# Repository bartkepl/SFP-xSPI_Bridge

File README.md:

# SFP-xSPI Bridge
## Mostek OCTOSPI / QUADSPI / SPI ↔ SFP na FPGA Gowin GW1N-9

Moduł łączący dwa mikrokontrolery STM32 łączem światłowodowym punkt–punkt, bez stosu IP. Host zapisuje i odczytuje ramki przez OCTOSPI, QUADSPI lub zwykłe SPI; FPGA koduje je w 8b/10b i wysyła przez moduł SFP z prędkością 100 Mbaud, a po drugiej stronie odzyskuje zegar programowo (soft-CDR z nadpróbkowaniem). Tryb przezroczysty UART pozwala użyć pary mostków jako „przedłużacza” portu szeregowego, bez żadnego sterownika.

> **Status:** projekt FPGA ukończony i zweryfikowany w symulacji (testy modułów i testy end-to-end dwóch kompletnych mostków), biblioteka C dla STM32 gotowa i przetestowana na modelu mostka, schemat i PCB rev. A zweryfikowane ([raport](doc/pcb-rev-a.md)), pliki produkcyjne wygenerowane — przed zamówieniem prototypu. Uruchomienie sprzętowe według [planu](doc/sfp-xspi-bridge-plan.md#9-plan-uruchomienia-bring-up).

```
STM32 ══ xSPI ══ GW1N-9 ══ LVDS ══ SFP ~~~ światłowód ~~~ SFP ══ LVDS ══ GW1N-9 ══ xSPI ══ STM32
```

---

## Płytka

<!-- Rendery generuje pcb/gen_media.kicad_jobset -->

| Góra (TOP) | Dół (BOTTOM) |
|---|---|
|  |  |

Płytka 4-warstwowa (JLC04161H-7628): pary LVDS na warstwie zewnętrznej nad ciągłą masą, płaszczyzna 3,3 V na warstwie wewnętrznej. Na płytce: klatka SFP, złącze hosta 2 × 10 (raster 1,27 mm), złącze programowania Tag-Connect TC2050 i zworka wyboru trybu. Zasilanie wyłącznie 3,3 V z hosta.

Wygenerowane PDF-y: [schemat](prod/sch/SFP_xSPI_Bridge.pdf) · [PCB](prod/pcb/SFP_xSPI_Bridge.pdf) · [interaktywny BOM](prod/ibom/SFP_xSPI_Bridge_ibom.html).

---

## Najważniejsze cechy

- **Łącze 100 Mbaud 8b/10b** przez standardowy moduł SFP bez wewnętrznego CDR (100BASE-FX / OC-3 lub 1000BASE-X, MM / SM, duplex lub BiDi).
- **Programowy odzysk zegara** — 4× nadpróbkowanie serializerami IDES8 (400 Msps), śledzenie fazy z histerezą, tolerancja odchyłki częstotliwości do ok. ±3900 ppm; oba końce na niezależnych generatorach, bez bufora elastycznego.
- **Ramki z CRC-32** (1–1024 B treści, pole TYPE do multipleksowania strumieni), kontrola przepływu XON/XOFF i gotowość odbiornika w sekwencji bezczynności — dane nie giną przy wolnym odbiorcy.
- **Interfejs hosta wzorowany na SPI NOR** — instrukcja i adres na 1 linii, dane na 1, 4 lub 8 liniach, SDR, tryb 0, SCLK do 40 MHz; współpracuje z OCTOSPI / XSPI / QUADSPI w trybie pośrednim i ze zwykłym SPI.
- **Spójne rejestry** — zatrzask przy opadnięciu CS, zapis stosowany po podniesieniu CS; FIFO TX 4 KiB i RX 8 KiB, przerwanie `HOST_IRQ_N`.
- **Tryb przezroczysty UART** — zworka lub rejestr; 8N1, 115 200 bit/s domyślnie, do ok. 3 Mbit/s, opcjonalnie RTS/CTS.
- **Zarządzanie modułem SFP** — I2C master w FPGA: pamięć A0h / A2h, automatyczny odczyt diagnostyki DDM, sygnały TX_DISABLE / TX_FAULT / LOS / MOD_ABS.
- **Diagnostyka łącza** — liczniki błędów kodu, CRC, długości, ramkowania, przepełnień i utrat synchronizacji; pętla zwrotna wewnątrz FPGA i echo ramek.
- **Biblioteka C dla STM32** konfigurowana przez `#define`, z portami HAL dla OCTOSPI, XSPI, QUADSPI i SPI.

---

## Specyfikacja

| Parametr | Wartość |
|---|---|
| FPGA | Gowin GW1N-UV9QN48C6/I5 (GW1N-9C), konfiguracja AUTOBOOT z wewnętrznej pamięci Flash |
| Łącze | 100 Mbaud, 8b/10b, ramki z CRC-32, bez retransmisji (błędy zgłaszane hostowi) |
| Przepustowość | do ok. 9,9 MB/s treści (ramki 1024 B) |
| Interfejs hosta | SPI 1-x-1, QSPI 1-0-4, OCTOSPI 1-0-8; SDR, tryb 0, SCLK ≤ 40 MHz |
| Bufory | FIFO TX 4 KiB, FIFO RX 8 KiB (BSRAM) |
| Tryb UART | 8N1, 115 200 bit/s (do ok. 3 Mbit/s), opcjonalnie RTS/CTS |
| Moduły SFP | INF-8074i, bez wewnętrznego CDR; SFP+ nieobsługiwane |
| Złącze hosta | 2 × 10, raster 1,27 mm: 3,3 V, SCLK, CS, IO0…IO7, DQS, IRQ, RST |
| Zasilanie | 3,3 V, ok. 0,45 A (moduł SFP do 300 mA) |
| PCB | 4 warstwy, 68 × 29,3 mm, 1,6 mm |
| Zajętość FPGA | 4483 LUT/ALU (52 %), 7 z 26 BSRAM; `clk_sys` 50 MHz (Fmax 56 MHz) |

---

## Architektura

```
             xSPI (SCLK ≤ 40 MHz)                                       LVDS 100 Mbaud
  STM32 ════════════════════════╗                                   ╔════════════════ SFP
                                ▼                                   │
          xspi_slave ─▶ csr_regs ─┬─▶ FIFO TX ─▶ framer + CRC ─▶ 8b/10b ─▶ OSER8 ─▶ TLVDS_OBUF ─▶ TD±
                                  │
                                  ├─◀ FIFO RX ◀─ deframer + CRC ◀─ 8b/10b ◀─ comma align ◀─ soft-CDR ◀─ IDES8 ◀─ RD±
                                  │
                                  ├─▶ I2C master + DDM ─▶ SFP SCL / SDA
                                  └─▶ sygnały SFP, LED, HOST_IRQ_N

  tryb UART:  UART_RX ─▶ pakietyzacja (ramki TYPE 0x01) ─▶ FIFO TX      FIFO RX ─▶ UART_TX
  zegary:     CLK_25M ─▶ rPLL 200 MHz (serializery) ─▶ CLKDIV /4 ─▶ clk_sys 50 MHz (logika)
```

Decyzje projektowe z uzasadnieniem: [rejestr ADR](doc/adr/README.md). Pełna koncepcja (piny, zegary, warstwa fizyczna, PCB, moduły, komendy, rejestry, uruchomienie): [`doc/sfp-xspi-bridge-plan.md`](doc/sfp-xspi-bridge-plan.md).

### Arkusze schematu

| Arkusz | Plik | Zawartość |
|---|---|---|
| root | [SFP_xSPI_Bridge.kicad_sch](pcb/SFP_xSPI_Bridge.kicad_sch) | połączenia hierarchiczne, otwory montażowe |
| EXT_IO | [ext_io.kicad_sch](pcb/ext_io.kicad_sch) | FPGA (zasilanie, konfiguracja, magistrala hosta), złącze hosta J3, Tag-Connect J2, zworki, TVS |
| SFP | [sfp.kicad_sch](pcb/sfp.kicad_sch) | klatka SFP, filtry zasilania modułu, terminacja i bias RX, generator 25 MHz, diody LED |

---

## Dokumentacja

| Dokument | Zawartość |
|---|---|
| [Interfejs hosta (datasheet)](doc/datasheet/index.md) | wyprowadzenia J3, parametry czasowe, komendy xSPI, mapa rejestrów, tryb UART, przykłady |
| [Biblioteka C (STM32)](doc/firmware.md) | konfiguracja, porty HAL, API, weryfikacja |
| [Koncepcja konstrukcji](doc/sfp-xspi-bridge-plan.md) | architektura, przydział pinów, zegary, PCB, moduły, uruchomienie |
| [Weryfikacja płytki rev. A](doc/pcb-rev-a.md) | DRC / ERC, zgodność z przydziałem pinów i INF-8074i, pary LVDS, zasilanie, pliki produkcyjne |
| [Projekt FPGA](doc/vhdl/index.md) | moduły VHDL, testbenche, symulacja, wyniki syntezy |
| [Testy end-to-end](doc/e2e/index.md) | dwa mostki połączone łączem: SPI, QSPI, OSPI, UART — z przebiegami |
| [Decyzje (ADR)](doc/adr/README.md) | kontekst, warianty i konsekwencje decyzji projektowych |

Dokumentacja jako serwis MkDocs (`mkdocs` 1.6, `mkdocs-material` 9.x):

```
python -m mkdocs serve        # podgląd: http://127.0.0.1:8000
```

---

## Szybki start

**FPGA** — Gowin EDA (projekt `vhdl/sfp_bridge/sfp_bridge.gprj`, VHDL-2008):

```
cd vhdl/sfp_bridge
gw_sh build.tcl               # synteza, PnR i bitstream
```

Bitstream: `vhdl/sfp_bridge/impl/pnr/sfp_bridge.fs`, programowanie przez JTAG (Gowin Programmer lub openFPGALoader).

**Symulacja** — GHDL 5 (VHDL-2008), na Windows w WSL; modele prymitywów z instalacji Gowin EDA:

```
$env:GOWIN_SIMLIB = "<Gowin EDA>\IDE\simlib\gw1n"   # PowerShell
cd vhdl\sim
.\run_tests.ps1               # wszystkie testbenche; .\view.ps1 <tb> — przebieg w GTKWave
```

**Firmware** — biblioteka w `firmware/sfp_bridge/`: skopiować `config/sfpb_config_template.h` jako `sfpb_config.h`, ustawić transport i uchwyt peryferium, wywołać `sfpb_init(&dev, NULL)`. Testy na PC: `make -C firmware/tests`.

**Bez hosta** — dwa mostki ze zwartą zworką `MODE_SEL` i dwa konwertery USB-UART (115 200 8N1) tworzą przezroczysty kanał szeregowy przez światłowód.

---

## Weryfikacja

| Obszar | Zakres | Wynik |
|---|---|---|
| Moduły FPGA | 24 samosprawdzające testbenche GHDL, testy mutacyjne | PASS |
| Łącze | dwa końce z odchyłką 200 ppm i jitterem, CDR do ±1000 ppm i ±0,3 UI | PASS |
| End-to-end | dwa kompletne mostki (modele prymitywów Gowin): SPI, QSPI, OSPI, UART zworką i rejestrem | PASS |
| Synteza | pełny układ, ograniczenia czasowe spełnione (`clk_sys` 56 MHz, `clk_host` 44 MHz) | OK |
| Biblioteka C | 207 sprawdzeń na modelu mostka, 17 mutacji wykrytych; kompilacja portów dla L4R5, H563, F446, L476, G0B1 | PASS |
| PCB | DRC i ERC bez błędów, przydział pinów 100 % zgodny z `.cst`, pary LVDS w regułach | OK |
| Sprzęt | uruchomienie prototypu rev. A | do wykonania |

---

## Roadmap

- [x] **Koncepcja** — architektura, dobór FPGA i modułów SFP, protokół łącza, interfejs hosta
- [x] **Schemat i PCB rev. A** w KiCad 10
- [x] **FPGA** — wszystkie moduły, integracja, ograniczenia czasowe, testy end-to-end
- [x] **Biblioteka C dla STM32** z testami na modelu mostka
- [x] **Weryfikacja płytki i pliki produkcyjne** rev. A
- [ ] **Zamówienie i montaż** prototypu
- [ ] **Uruchomienie** — konfiguracja FPGA, tryb UART przez światłowód, xSPI, I2C / DDM
- [ ] **Pomiary** — wykres oczkowy RD±, BER ≥ 10¹² bitów, różne moduły i tłumiki optyczne
- [ ] **Rozszerzenia** — 125 Mbaud, kolejna rewizja PCB z uwagami z uruchomienia

---

## Struktura repozytorium

```
.
├── doc/          # dokumentacja (MkDocs): koncepcja, datasheet, ADR, opisy modułów, testy end-to-end
├── firmware/     # biblioteka C dla STM32 (sfp_bridge), przykład, testy na PC
├── media/        # rendery 3D płytki
├── pcb/          # projekt KiCad 10 (schemat hierarchiczny, PCB, reguły DRC, biblioteka lokalna, jobsety)
├── prod/         # pliki produkcyjne: Gerbery (.zip), PDF schematu i PCB, interaktywny BOM
└── vhdl/         # projekt FPGA (Gowin EDA): źródła, ograniczenia, testbenche i skrypty symulacji
```

Pliki produkcyjne generują jobsety KiCad: [gen_prod.kicad_jobset](pcb/gen_prod.kicad_jobset) (PDF, BOM), [gen_gerber.kicad_jobset](pcb/gen_gerber.kicad_jobset) (Gerbery, wiercenia), [gen_media.kicad_jobset](pcb/gen_media.kicad_jobset) (rendery 3D).

---

## Referencje

- Gowin Semiconductor: DS100 (GW1N series), UG114 (GW1N-9 pinout), UG286 (zegary), UG289 (programowalne I/O), UG290 (programowanie i konfiguracja), UG284 (schematy), SUG935 (ograniczenia fizyczne)
- SFF Committee: INF-8074i (SFP MSA), SFF-8472 (diagnostyka modułów SFP)
- IEEE 802.3, klauzula 36 (kod 8b/10b, 1000BASE-X PCS)
- AMD/Xilinx XAPP224, XAPP523 — odzysk danych z nadpróbkowania
- STMicroelectronics: dokumentacja peryferiów OCTOSPI / XSPI / QUADSPI i sterowników HAL STM32Cube

---

## Licencja

[MIT](LICENSE) © 2026 bartkepl

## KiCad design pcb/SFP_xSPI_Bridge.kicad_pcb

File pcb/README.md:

# pcb

Projekt płytki w KiCad: FPGA GW1N-UV4QN48, klatka SFP z filtrami zasilania wg SFF-8431, generator 25 MHz, złącze hosta 2 × 10 / 1,27 mm, złącze JTAG 1 × 6.

Wymagania elektryczne i reguły layoutu: [`../doc/sfp-xspi-bridge-plan.md`](../doc/sfp-xspi-bridge-plan.md), rozdział 5.

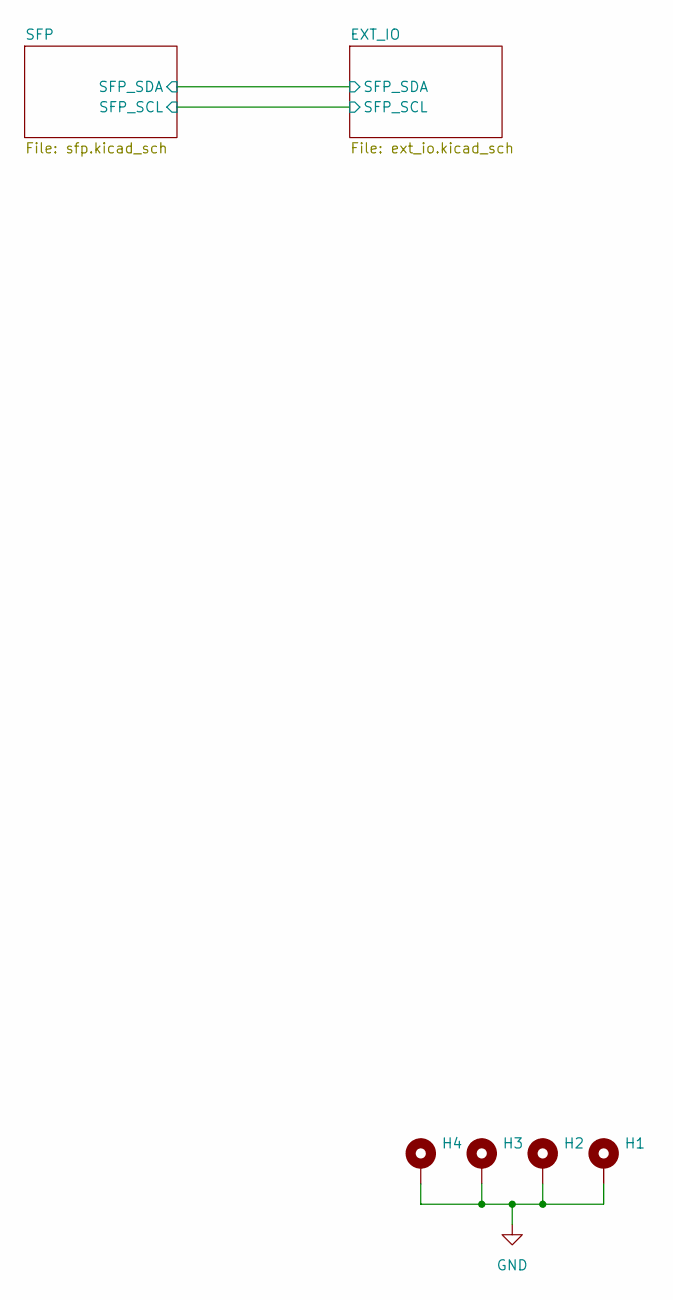
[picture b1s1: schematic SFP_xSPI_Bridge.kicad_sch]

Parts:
H1, H2, H3, H4: MountingHole_Pad; MountingHole_2.7mm_M2.5_DIN965_Pad

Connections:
GND: H1.1 (1_1), H2.1 (1_1), H3.1 (1_1), H4.1 (1_1); also elsewhere on the board

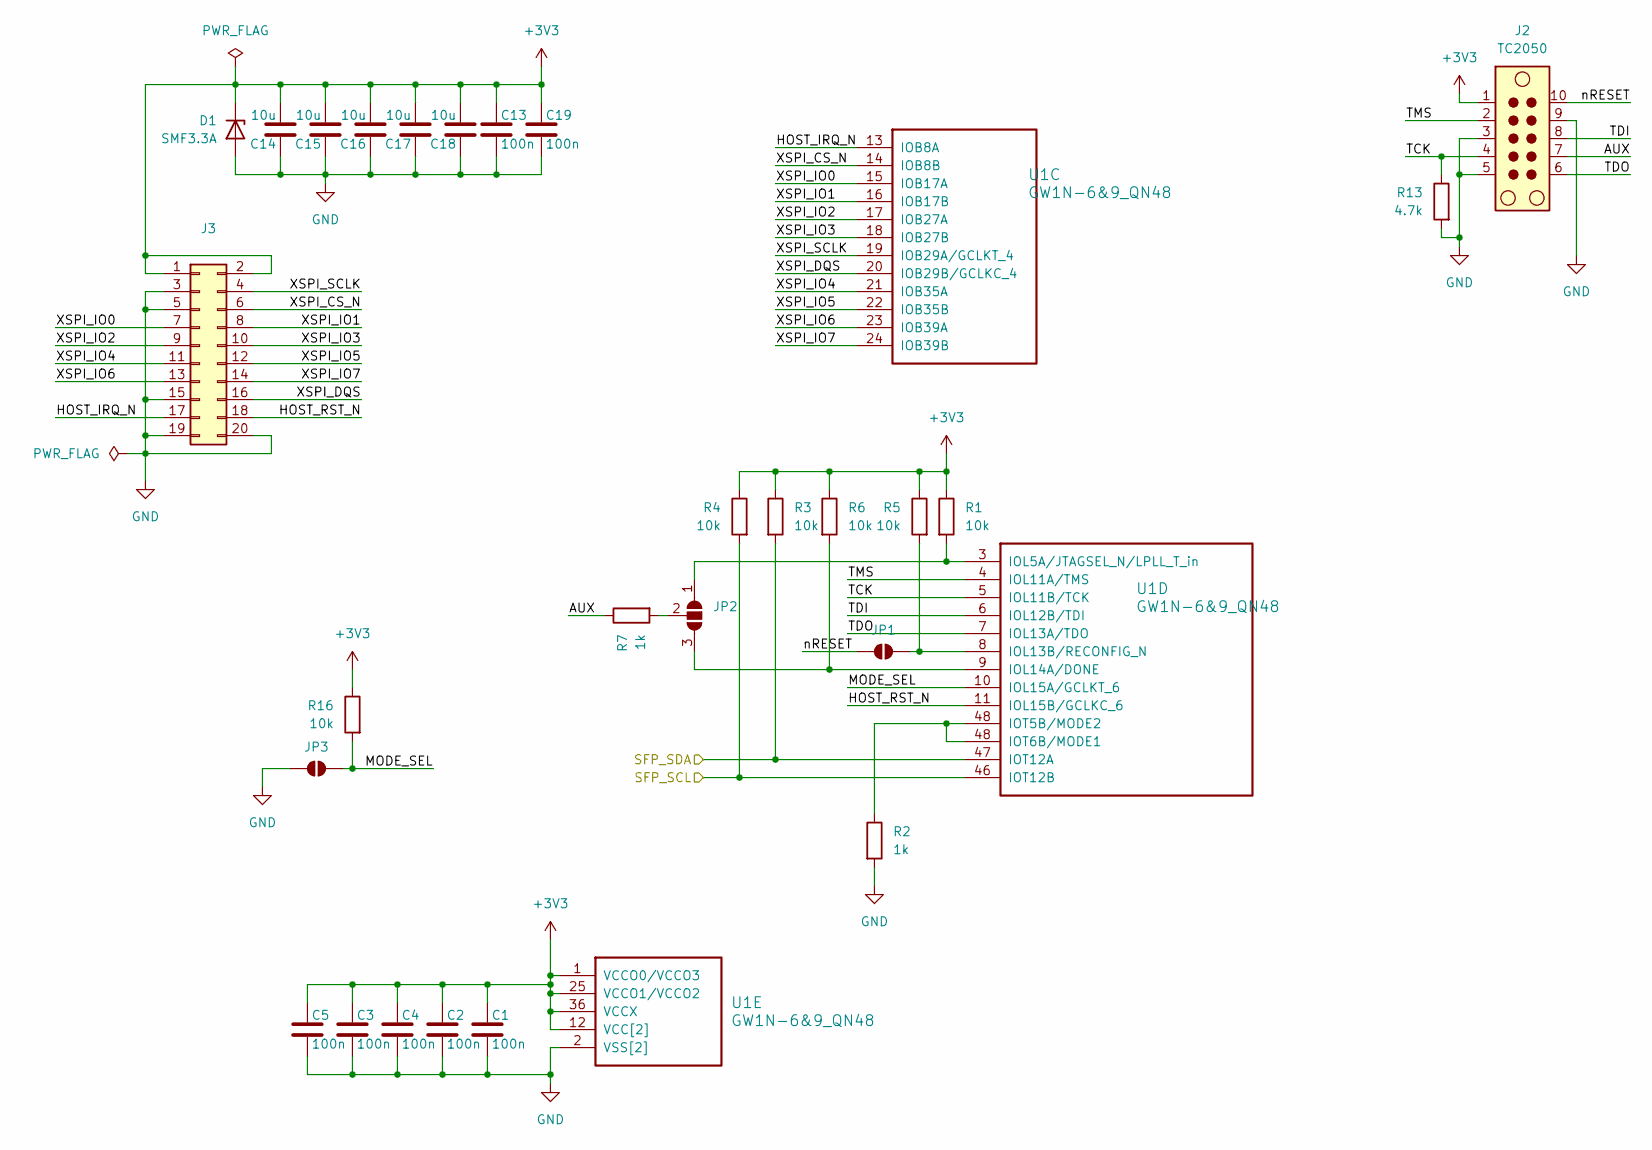
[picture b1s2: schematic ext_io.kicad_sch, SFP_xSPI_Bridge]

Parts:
C1, C2, C3, C4, C5, C13, C19: 100n; C_0603_1608Metric
C14, C15, C16, C17, C18: 10u; C_0603_1608Metric
D1: SMF3.3A; D_SOD-123F
J2: TC2050; Tag-Connect_TC2050-IDC-NL_2x05_P1.27mm_Vertical
J3: Conn_02x10_Odd_Even; PinHeader_2x10_P1.27mm_Vertical
JP1, JP3: SolderJumper_2_Open; SolderJumper-2_P1.3mm_Open_TrianglePad1.0x1.5mm
JP2: SolderJumper_3_Open; SolderJumper-3_P2.0mm_Open_TrianglePad1.0x1.5mm
R1, R3, R4, R5, R6, R16: 10k; R_0603_1608Metric
R2, R7: 1k; R_0603_1608Metric
R13: 4.7k; R_0603_1608Metric
U1: GW1N-6&9_QN48; QFN-48-1EP_6x6mm_P0.4mm_EP4.2x4.2mm_ThermalVias

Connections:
+3V3: C1.1, C2.1, C3.1, C4.1, C5.1, C13.1, C14.2, C15.2, C16.2, C17.2, C18.2, C19.1, D1.1 (K), J2.1, J3.1, J3.2, R1.1, R3.1, R4.1, R5.1, R6.1, R16.1, U1.1 (VCCO0/VCCO3), U1.12 (VCC[2]), U1.25 (VCCO1/VCCO2), U1.36 (VCCX), U1.37 (VCC[2]); also elsewhere on the board
/EXT_IO/AUX: J2.7, R7.1
/EXT_IO/HOST_IRQ_N: J3.17, U1.13 (IOB8A)
/EXT_IO/HOST_RST_N: J3.18, U1.11 (IOL15B/GCLKC_6)
/EXT_IO/MODE_SEL: JP3.2 (B), R16.2, U1.10 (IOL15A/GCLKT_6)
/EXT_IO/SFP_SCL: R4.2, U1.46 (IOT12B); also elsewhere on the board
/EXT_IO/SFP_SDA: R3.2, U1.47 (IOT12A); also elsewhere on the board
/EXT_IO/TCK: J2.4, R13.1, U1.5 (IOL11B/TCK)
/EXT_IO/TDI: J2.8, U1.6 (IOL12B/TDI)
/EXT_IO/TDO: J2.6, U1.7 (IOL13A/TDO)
/EXT_IO/TMS: J2.2, U1.4 (IOL11A/TMS)
/EXT_IO/XSPI_CS_N: J3.6, U1.14 (IOB8B)
/EXT_IO/XSPI_DQS: J3.16, U1.20 (IOB29B/GCLKC_4)
/EXT_IO/XSPI_IO0: J3.7, U1.15 (IOB17A)
/EXT_IO/XSPI_IO1: J3.8, U1.16 (IOB17B)
/EXT_IO/XSPI_IO2: J3.9, U1.17 (IOB27A)
/EXT_IO/XSPI_IO3: J3.10, U1.18 (IOB27B)
/EXT_IO/XSPI_IO4: J3.11, U1.21 (IOB35A)
/EXT_IO/XSPI_IO5: J3.12, U1.22 (IOB35B)
/EXT_IO/XSPI_IO6: J3.13, U1.23 (IOB39A)
/EXT_IO/XSPI_IO7: J3.14, U1.24 (IOB39B)
/EXT_IO/XSPI_SCLK: J3.4, U1.19 (IOB29A/GCLKT_4)
/EXT_IO/nRESET: J2.10, JP1.1 (A)
GND: C1.2, C2.2, C3.2, C4.2, C5.2, C13.2, C14.1, C15.1, C16.1, C17.1, C18.1, C19.2, D1.2 (A), J2.3, J2.5, J2.9, J3.3, J3.5, J3.15, J3.19, J3.20, JP3.1 (A), R2.2, R13.2, U1.2 (VSS[2]), U1.26 (VSS[2]), U1.49 (EPAD); also elsewhere on the board
unnamed: JP1.2 (B), R5.2, U1.8 (IOL13B/RECONFIG_N)
unnamed: JP2.1 (A), R1.2, U1.3 (IOL5A/JTAGSEL_N/LPLL_T_in)
unnamed: JP2.3 (B), R6.2, U1.9 (IOL14A/DONE)
unnamed: JP2.2 (C), R7.2
unnamed: R2.1, U1.48 (IOT5B/MODE2)

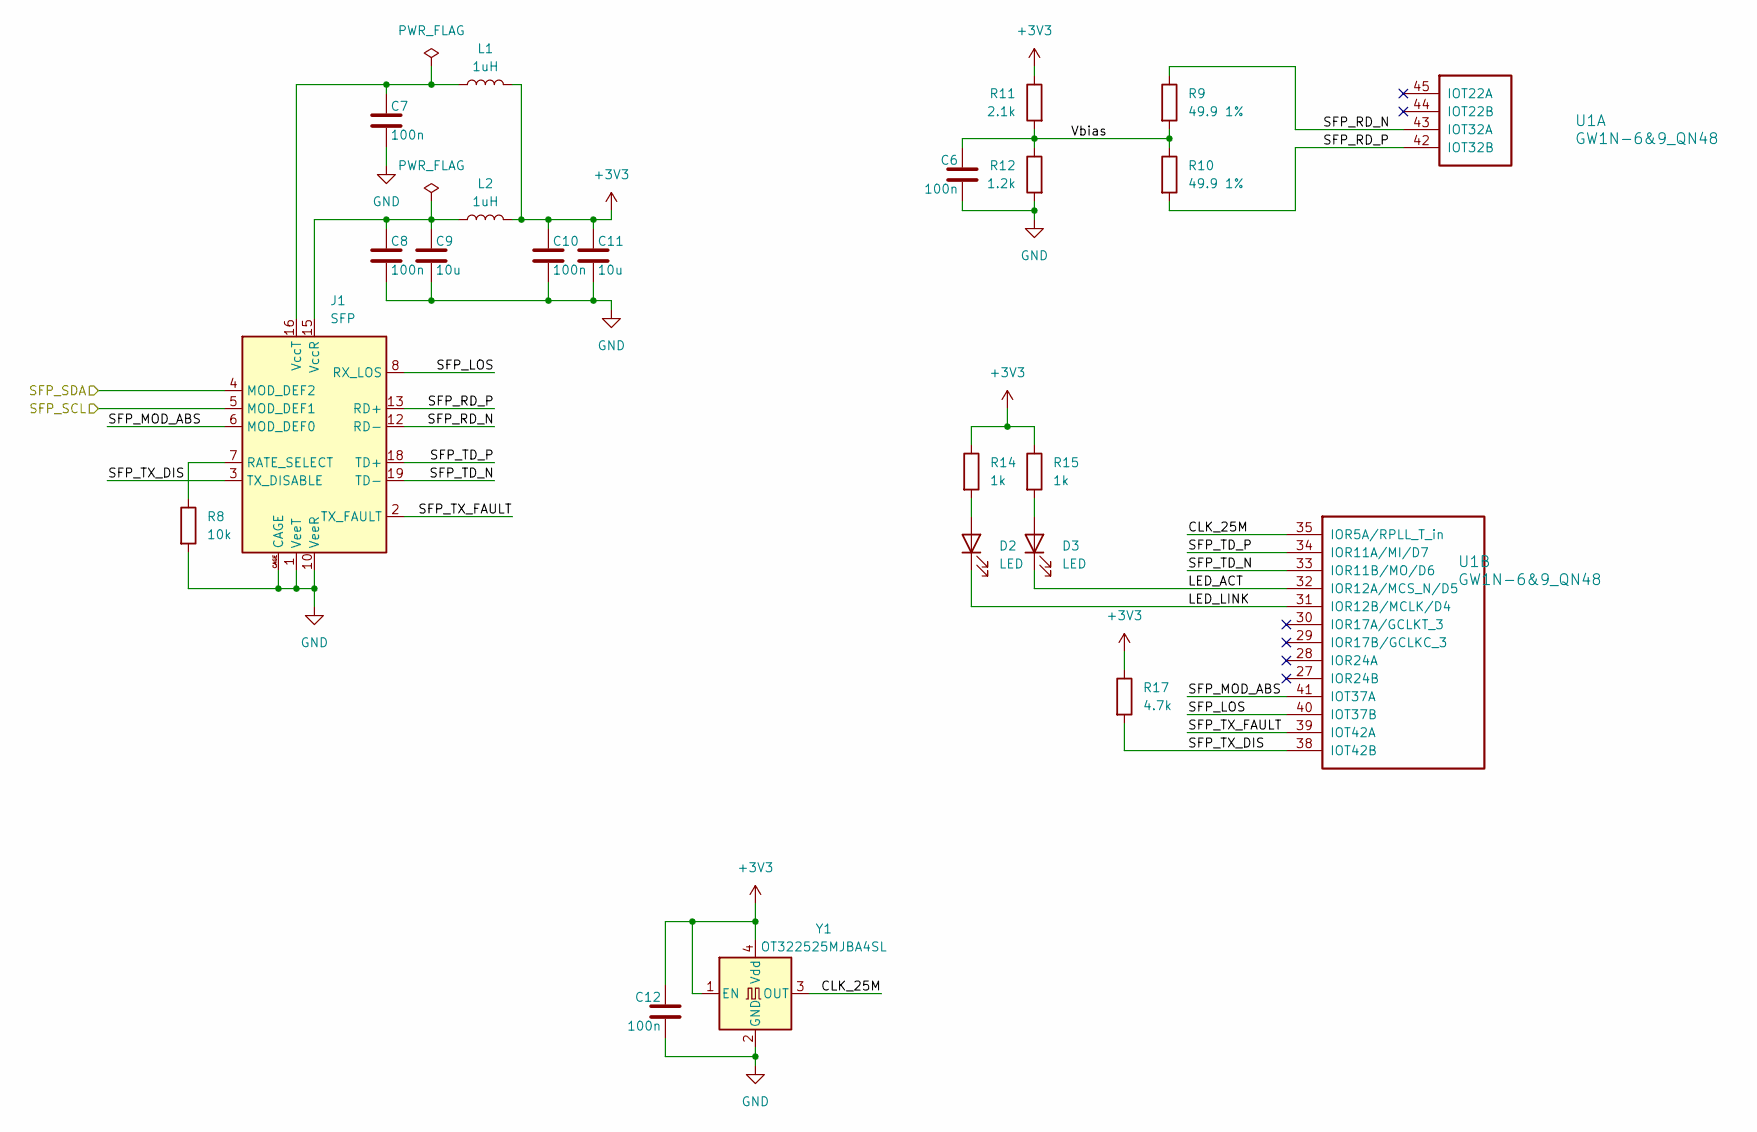
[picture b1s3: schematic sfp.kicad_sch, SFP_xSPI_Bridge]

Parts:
C6, C7, C8, C10, C12: 100n; C_0603_1608Metric
C9, C11: 10u; C_0603_1608Metric
D2: LED; LED_0603_1608Metric; MPN XL-1608SYGC-06; LCSC C965805
D3: LED; LED_0603_1608Metric; MPN XL-1608UOC-06; LCSC C965800
J1: SFP; Connector_SFP_and_Cage
L1, L2: 1uH; L_0805_2012Metric; MPN NL05KTC1R0
R8: 10k; R_0603_1608Metric
R9, R10: 49.9 1%; R_0402_1005Metric
R11: 2.1k; R_0603_1608Metric
R12: 1.2k; R_0603_1608Metric
R14, R15: 1k; R_0603_1608Metric
R17: 4.7k; R_0603_1608Metric
U1: GW1N-6&9_QN48; QFN-48-1EP_6x6mm_P0.4mm_EP4.2x4.2mm_ThermalVias
Y1: OT322525MJBA4SL; Oscillator_SMD_Abracon_ASE-4Pin_3.2x2.5mm; MPN OT322525MJBA4SL; LCSC C669088

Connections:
+3V3: C10.1, C11.1, C12.1, L1.2, L2.2, R11.1, R14.1, R15.1, R17.1, Y1.1 (EN), Y1.4 (Vdd); also elsewhere on the board
/EXT_IO/SFP_SCL: J1.5 (MOD_DEF1); also elsewhere on the board
/EXT_IO/SFP_SDA: J1.4 (MOD_DEF2); also elsewhere on the board
/SFP/CLK_25M: U1.35 (IOR5A/RPLL_T_in), Y1.3 (OUT)
/SFP/LED_ACT: D3.1 (K), U1.32 (IOR12A/MCS_N/D5)
/SFP/LED_LINK: D2.1 (K), U1.31 (IOR12B/MCLK/D4)
/SFP/SFP_LOS: J1.8 (RX_LOS), U1.40 (IOT37B)
/SFP/SFP_MOD_ABS: J1.6 (MOD_DEF0), U1.41 (IOT37A)
/SFP/SFP_RD_N: J1.12 (RD-), R9.1, U1.43 (IOT32A)
/SFP/SFP_RD_P: J1.13 (RD+), R10.2, U1.42 (IOT32B)
/SFP/SFP_TD_N: J1.19 (TD-), U1.33 (IOR11B/MO/D6)
/SFP/SFP_TD_P: J1.18 (TD+), U1.34 (IOR11A/MI/D7)
/SFP/SFP_TX_DIS: J1.3 (TX_DISABLE), R17.2, U1.38 (IOT42B)
/SFP/SFP_TX_FAULT: J1.2 (TX_FAULT), U1.39 (IOT42A)
/SFP/Vbias: C6.1, R9.2, R10.1, R11.2, R12.1
GND: C6.2, C7.2, C8.2, C9.2, C10.2, C11.2, C12.2, J1.1 (VeeT), J1.9 (VeeR), J1.10 (VeeR), J1.11 (VeeR), J1.14 (VeeR), J1.17 (VeeT), J1.20 (VeeT), J1.CAGE, R8.2, R12.2, Y1.2 (GND); also elsewhere on the board
unnamed: D2.2 (A), R14.2
unnamed: D3.2 (A), R15.2
unnamed: J1.7 (RATE_SELECT), R8.1
unnamed: C8.1, C9.1, J1.15 (VccR), L2.1
unnamed: C7.1, J1.16 (VccT), L1.1

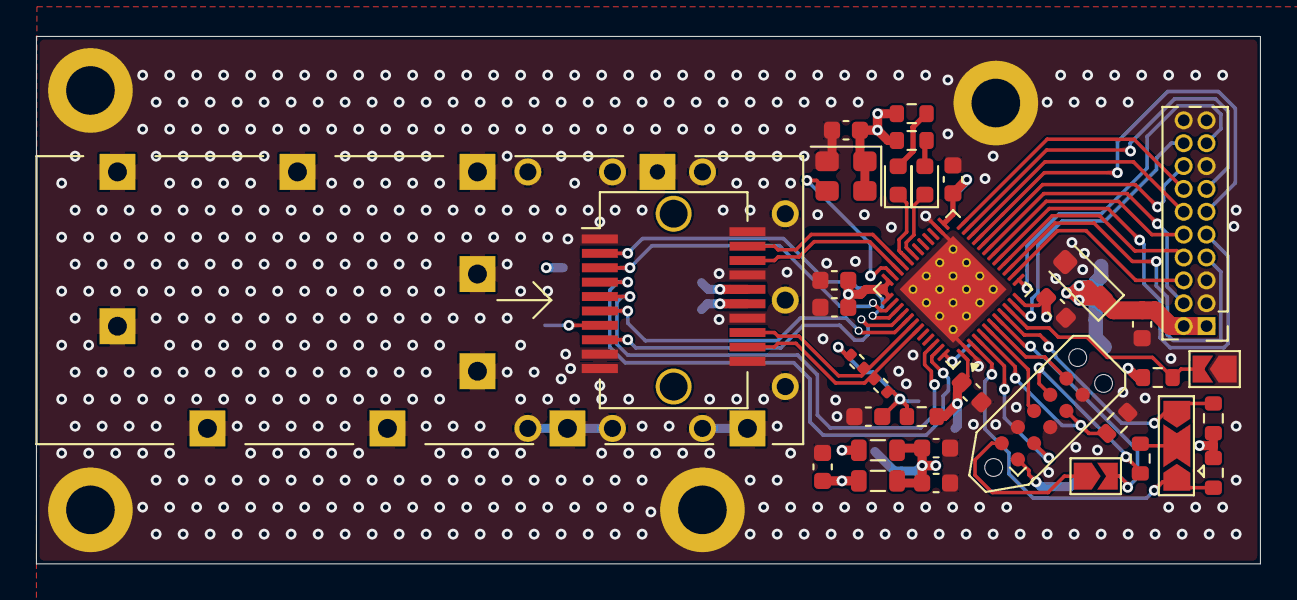
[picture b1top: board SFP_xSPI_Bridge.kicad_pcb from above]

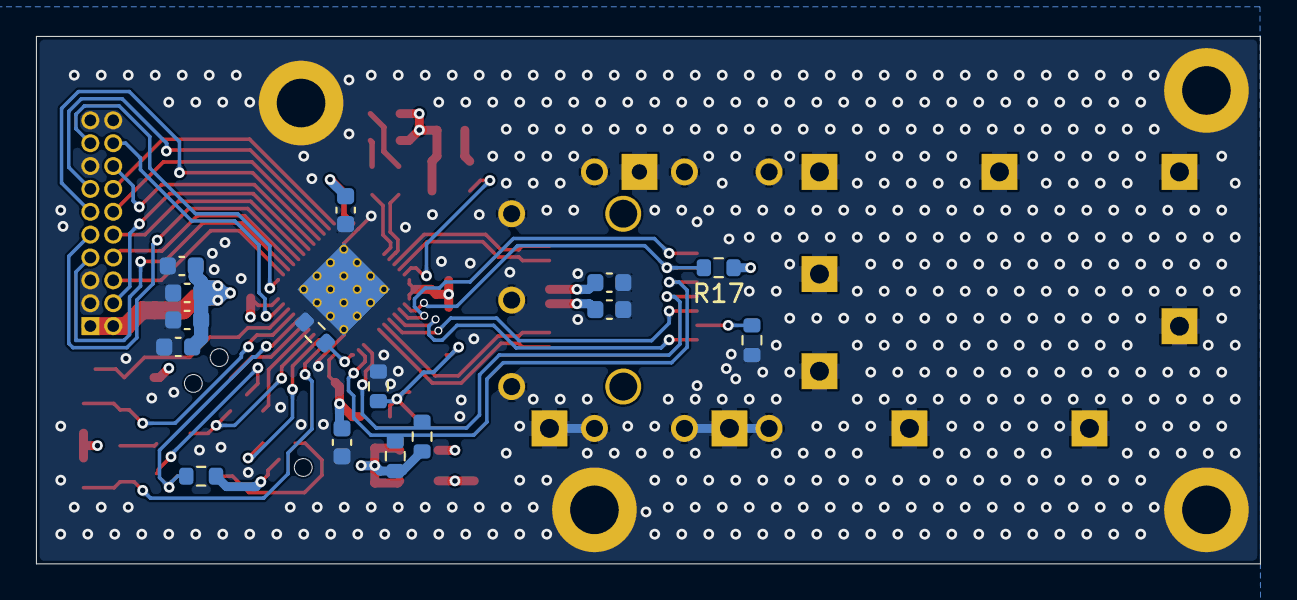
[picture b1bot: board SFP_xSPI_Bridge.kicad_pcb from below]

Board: 4 copper layers, 68.0 x 29.3 mm, 53 parts (15 on the bottom side), 46 nets.
